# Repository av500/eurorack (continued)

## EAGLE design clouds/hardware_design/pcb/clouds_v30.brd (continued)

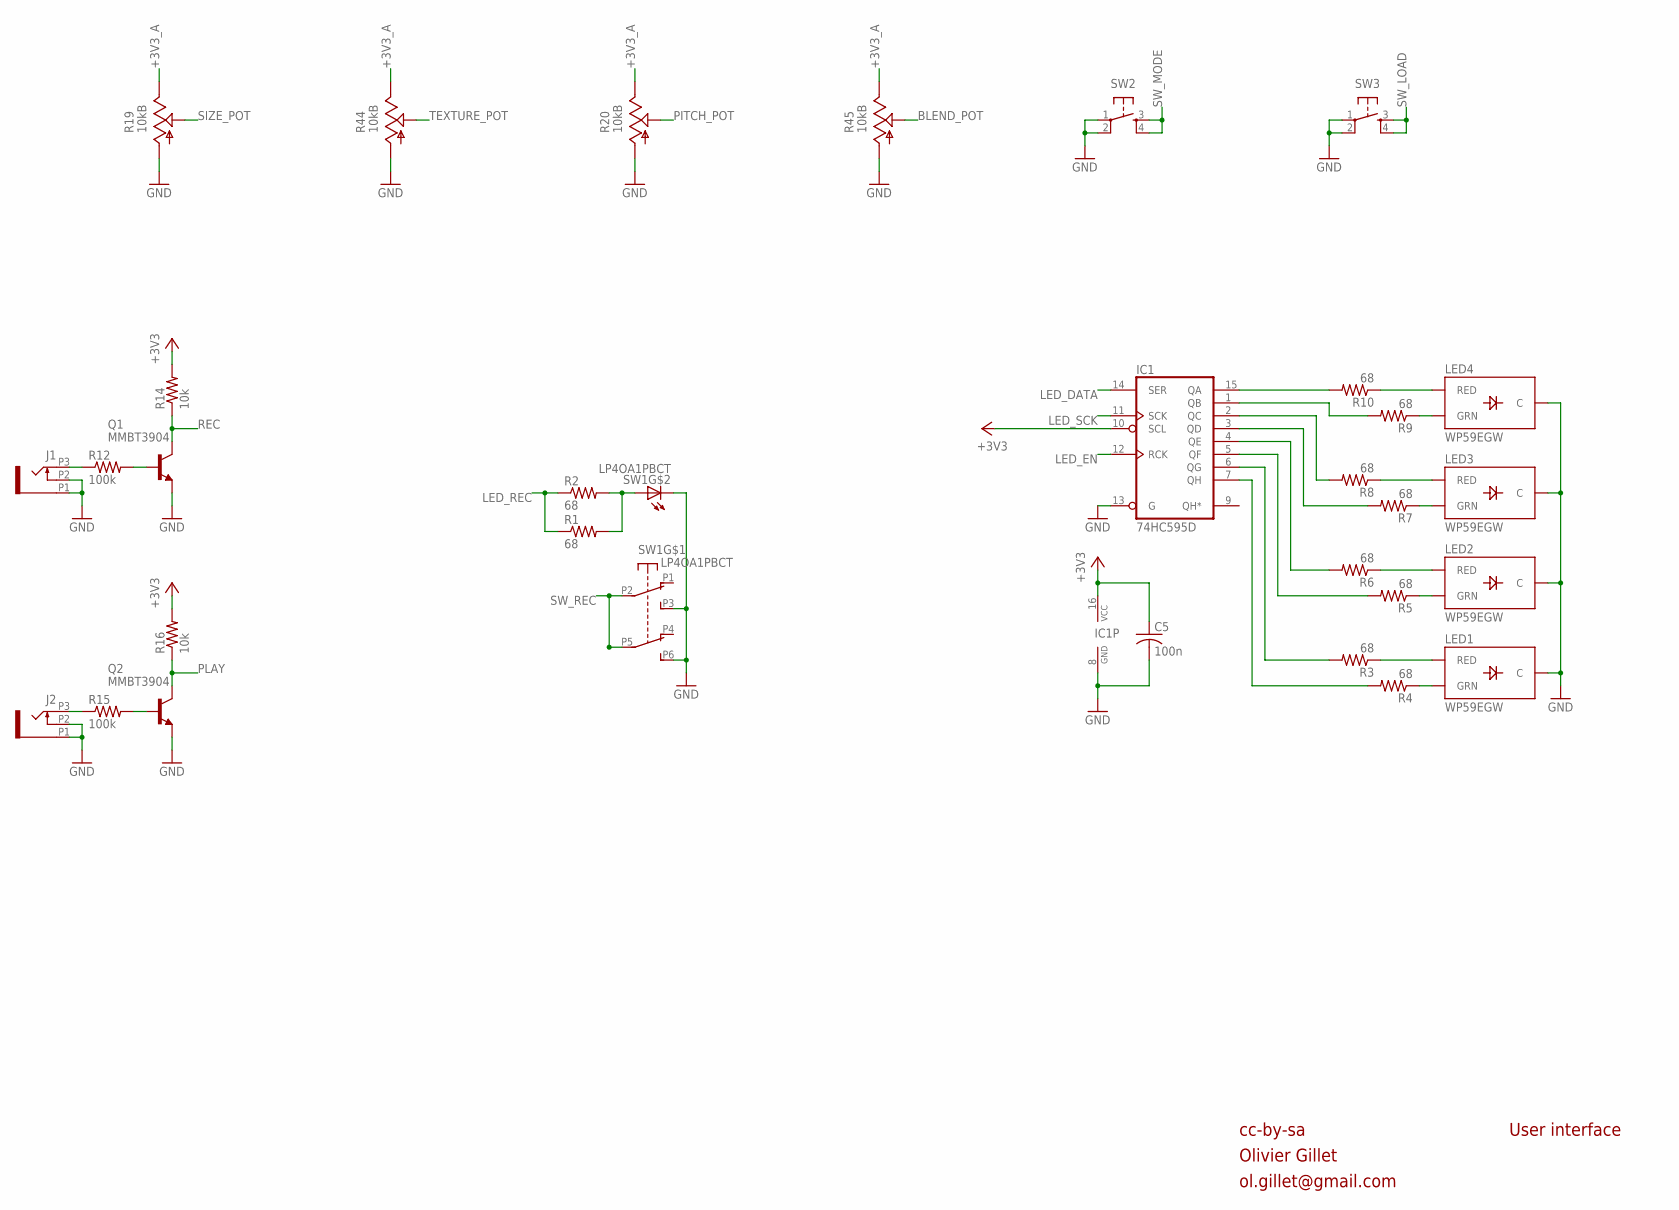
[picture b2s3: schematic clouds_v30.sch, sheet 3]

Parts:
C5: 100n; C0603
IC1: 74HC595D; SO16
J1, J2: PJ301_THONKICONN6; WQP_PJ_301M6
LED1, LED2, LED3, LED4: WP59EGW; LED-BICOLOR-THROUGHHOLE-5MM
Q1, Q2: MMBT3904; SOT23-BEC
R1, R2, R3, R4, R5, R6, R7, R8, R9, R10: 68; R0603
R12, R15: 100k; R0603
R14, R16: 10k; R0603
R19, R20, R44, R45: 10kB; ALPS_POT_VERTICAL_PS
SW1: LP4OA1PBCT
SW2, SW3: TAC_SWITCHPTH; TACTILE-PTH

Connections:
+3V3: C5.1, IC1.10 (SCL), IC1.16 (VCC), R14.2, R16.2; also elsewhere on the board
+3V3_A: R19.P$1 (E), R20.P$1 (E), R44.P$1 (E), R45.P$1 (E); also elsewhere on the board
BLEND_POT: R45.P$2 (S); also elsewhere on the board
GND: C5.2, IC1.8 (GND), IC1.13 (G), J1.P1 (1), J1.P2 (2), J2.P1 (1), J2.P2 (2), LED1.2 (C), LED2.2 (C), LED3.2 (C), LED4.2 (C), Q1.E, Q2.E, R19.P$3 (A), R20.P$3 (A), R44.P$3 (A), R45.P$3 (A), SW1.L2, SW1.P3 (A3), SW1.P6 (B3), SW2.1, SW2.2, SW3.1, SW3.2; also elsewhere on the board
LED_DATA: IC1.14 (SER); also elsewhere on the board
LED_EN: IC1.12 (RCK); also elsewhere on the board
LED_REC: R1.1, R2.1; also elsewhere on the board
LED_SCK: IC1.11 (SCK); also elsewhere on the board
unnamed: LED4.3 (GRN), R9.1
unnamed: LED4.1 (RED), R10.1
unnamed: LED3.1 (RED), R8.1
unnamed: LED3.3 (GRN), R7.1
unnamed: LED2.1 (RED), R6.1
unnamed: J2.P3 (3), R15.1
unnamed: Q2.B, R15.2
unnamed: R1.2, R2.2, SW1.L1
unnamed: LED2.3 (GRN), R5.1
unnamed: LED1.1 (RED), R3.1
unnamed: LED1.3 (GRN), R4.1
unnamed: IC1.15 (QA), R10.2
unnamed: IC1.1 (QB), R9.2
unnamed: IC1.2 (QC), R8.2
unnamed: IC1.3 (QD), R7.2
unnamed: IC1.4 (QE), R6.2
unnamed: IC1.5 (QF), R5.2
unnamed: IC1.6 (QG), R3.2
unnamed: IC1.7 (QH), R4.2
unnamed: J1.P3 (3), R12.1
unnamed: Q1.B, R12.2
PITCH_POT: R20.P$2 (S); also elsewhere on the board
PLAY: Q2.C, R16.1; also elsewhere on the board
REC: Q1.C, R14.1; also elsewhere on the board
SIZE_POT: R19.P$2 (S); also elsewhere on the board
SW_LOAD: SW3.3, SW3.4; also elsewhere on the board
SW_MODE: SW2.3, SW2.4; also elsewhere on the board
SW_REC: SW1.P2 (A2), SW1.P5 (B2); also elsewhere on the board
TEXTURE_POT: R44.P$2 (S); also elsewhere on the board

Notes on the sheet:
cc-by-sa
Olivier Gillet
ol.gillet@gmail.com
User interface

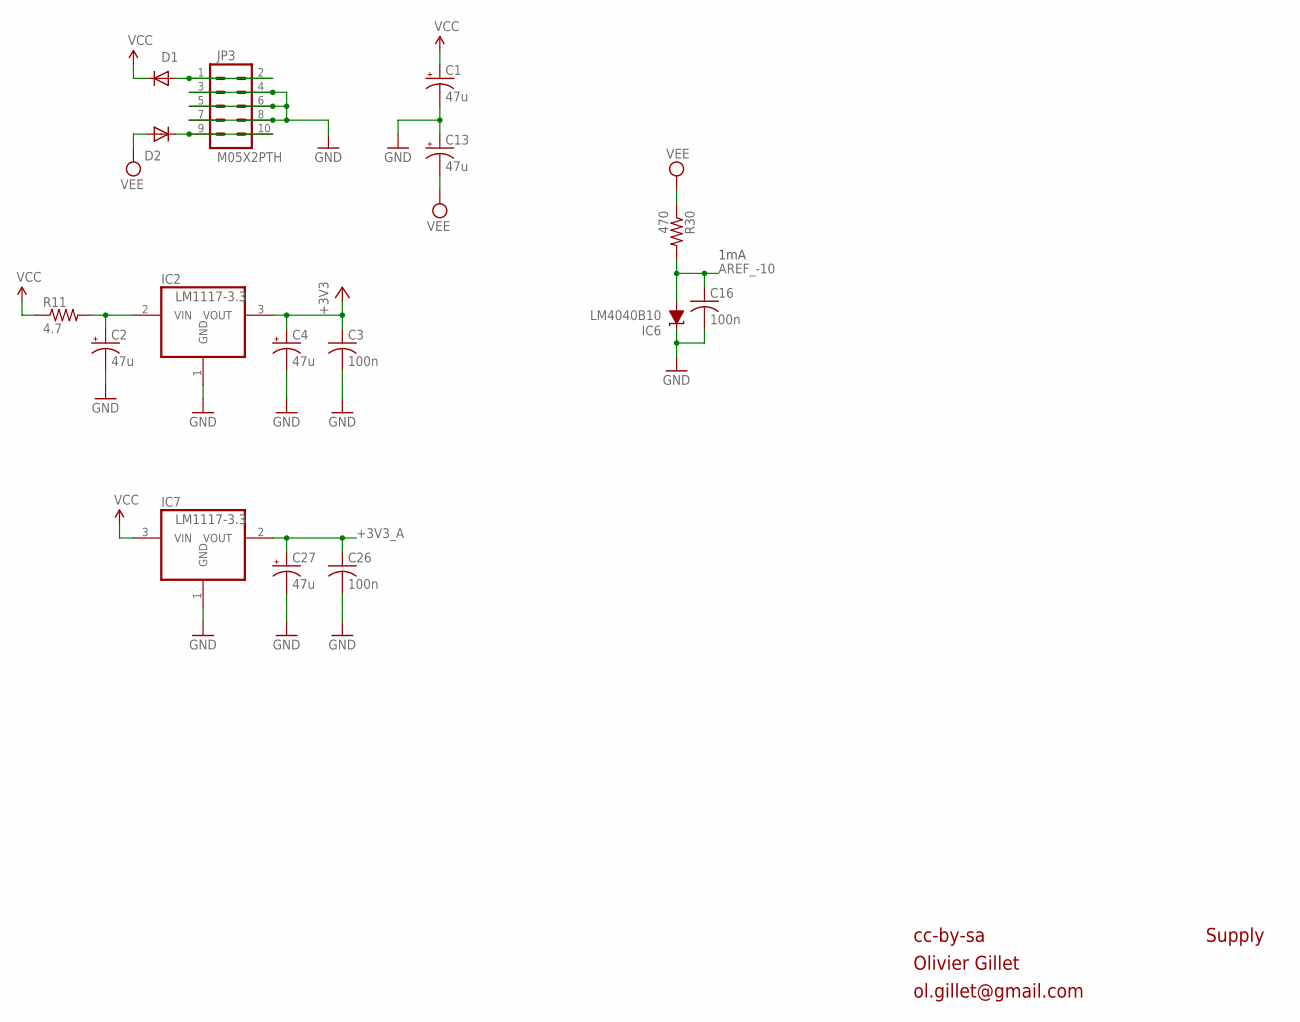
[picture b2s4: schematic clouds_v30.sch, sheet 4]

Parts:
C1, C2, C4, C13, C27: 47u; PANASONIC_D
C3, C16, C26: 100n; C0603
D1, D2: 1N5819HW; SOD123
IC2: LM1117-3.3; TO252
IC6: LM4040B10; DBZ_R-PDSO-G3
IC7: LM1117-3.3; SOT223
JP3: M05X2PTH; AVR_ICSP
R11: 4.7; R1206
R30: 470; R0603

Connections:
+3V3: C3.1, C4.+, IC2.3 (VOUT); also elsewhere on the board
+3V3_A: C26.1, C27.+, IC7.2 (VOUT); also elsewhere on the board
AREF_-10: C16.1, IC6.2 (A), R30.2; also elsewhere on the board
GND: C1.-, C2.-, C3.2, C4.-, C13.+, C16.2, C26.2, C27.-, IC2.1 (GND), IC6.1 (C), IC7.1 (GND), JP3.3, JP3.4, JP3.5, JP3.6, JP3.7, JP3.8; also elsewhere on the board
unnamed: C2.+, IC2.2 (VIN), R11.2
unnamed: D1.A, JP3.1, JP3.2
unnamed: D2.C, JP3.9, JP3.10
VCC: C1.+, D1.C, IC7.3 (VIN), R11.1; also elsewhere on the board
VEE: C13.-, D2.A, R30.1; also elsewhere on the board

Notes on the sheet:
1mA
cc-by-sa
Olivier Gillet
ol.gillet@gmail.com
Supply

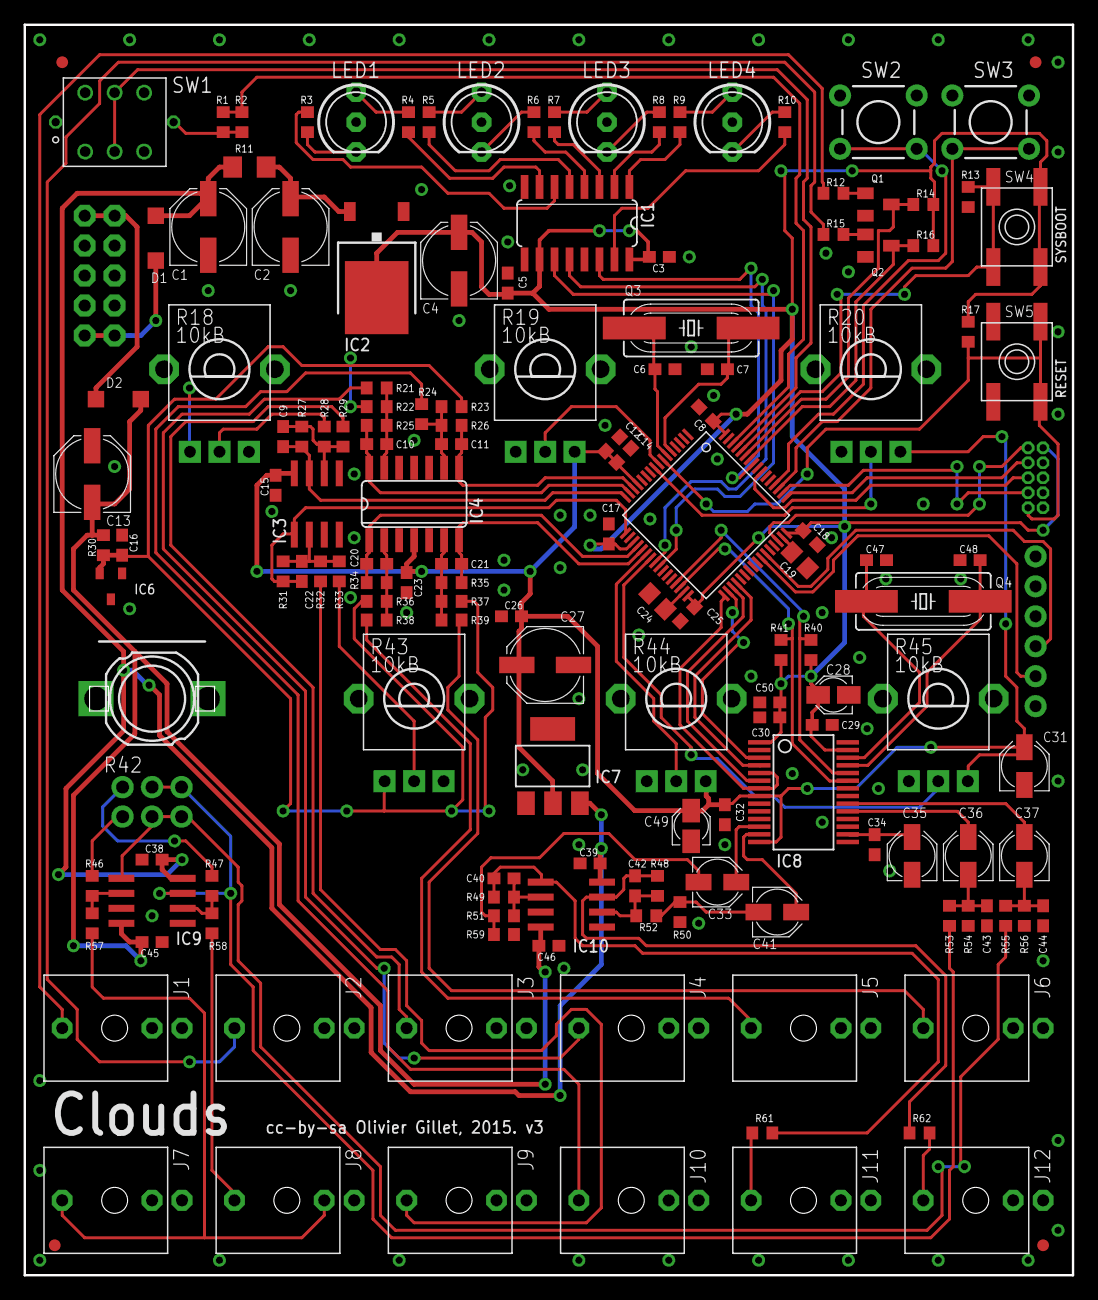
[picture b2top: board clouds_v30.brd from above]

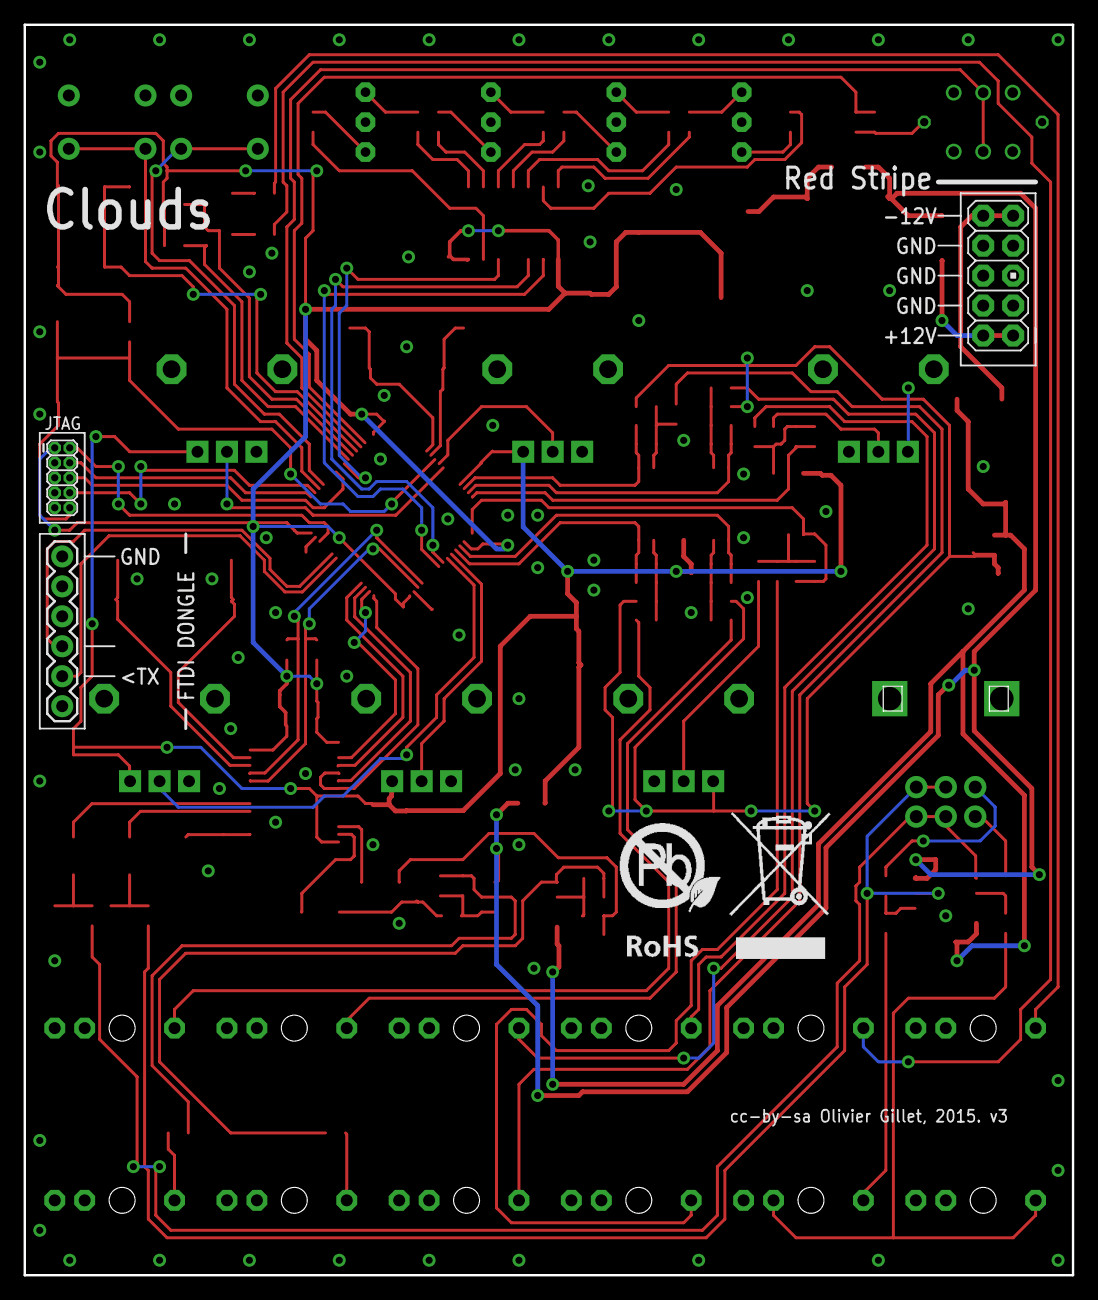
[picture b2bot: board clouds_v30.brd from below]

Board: 2 copper layers, 88.9 x 106.0 mm, 156 parts (4 on the bottom side), 106 nets.

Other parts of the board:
U$2: ROHS_BIG

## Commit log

2016-11-21 convert clouds to new eagle XML format
2016-11-21 convert R42 from BOURNS_PTV112 to ALPHA_RD902F-040
2016-11-27 save braids in new XML format
2016-11-27 make the encoder A/B orientation a build time setting with solder jumpers
2017-03-24 add a 6-pin combined SWD/UART header
